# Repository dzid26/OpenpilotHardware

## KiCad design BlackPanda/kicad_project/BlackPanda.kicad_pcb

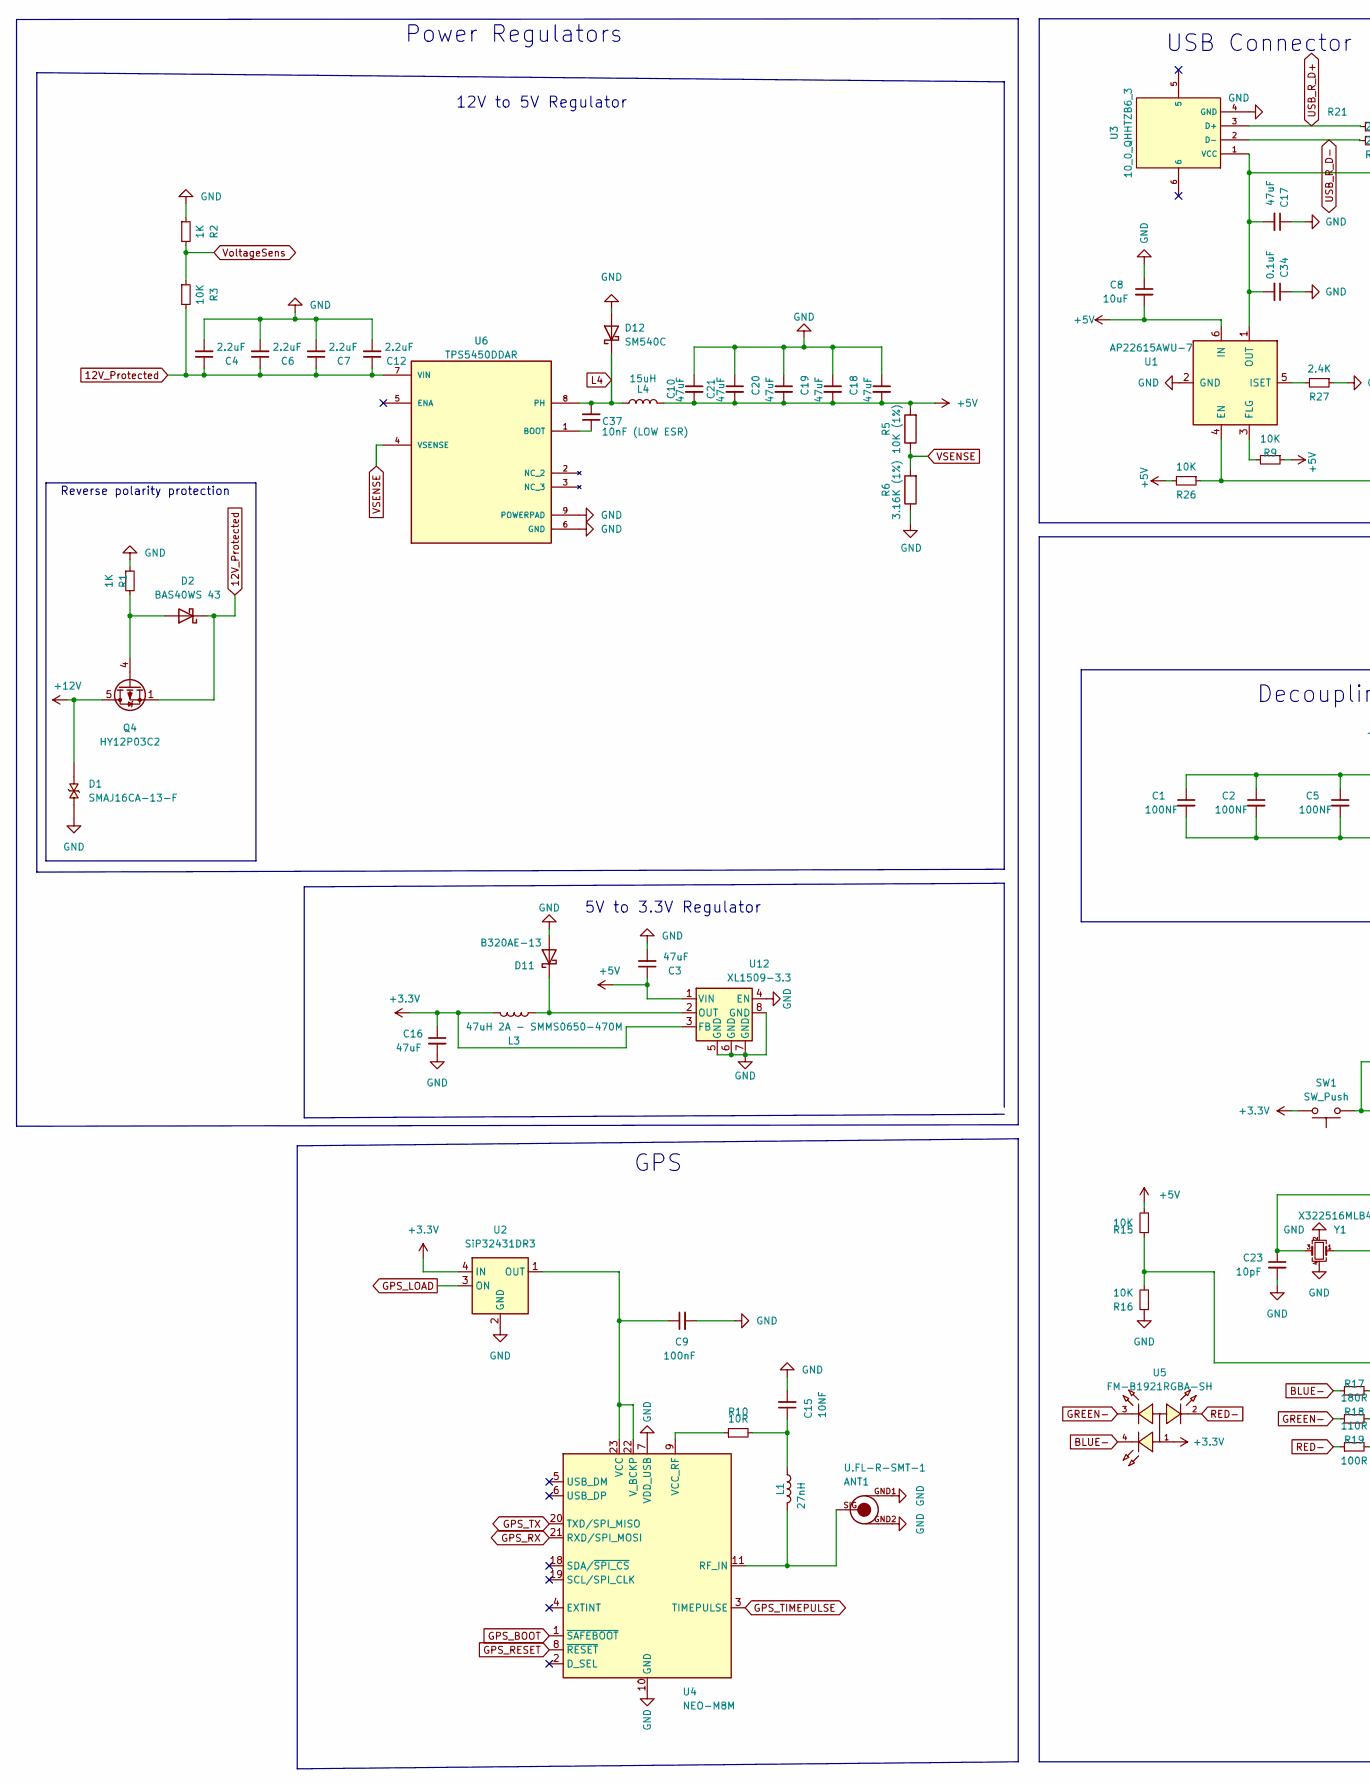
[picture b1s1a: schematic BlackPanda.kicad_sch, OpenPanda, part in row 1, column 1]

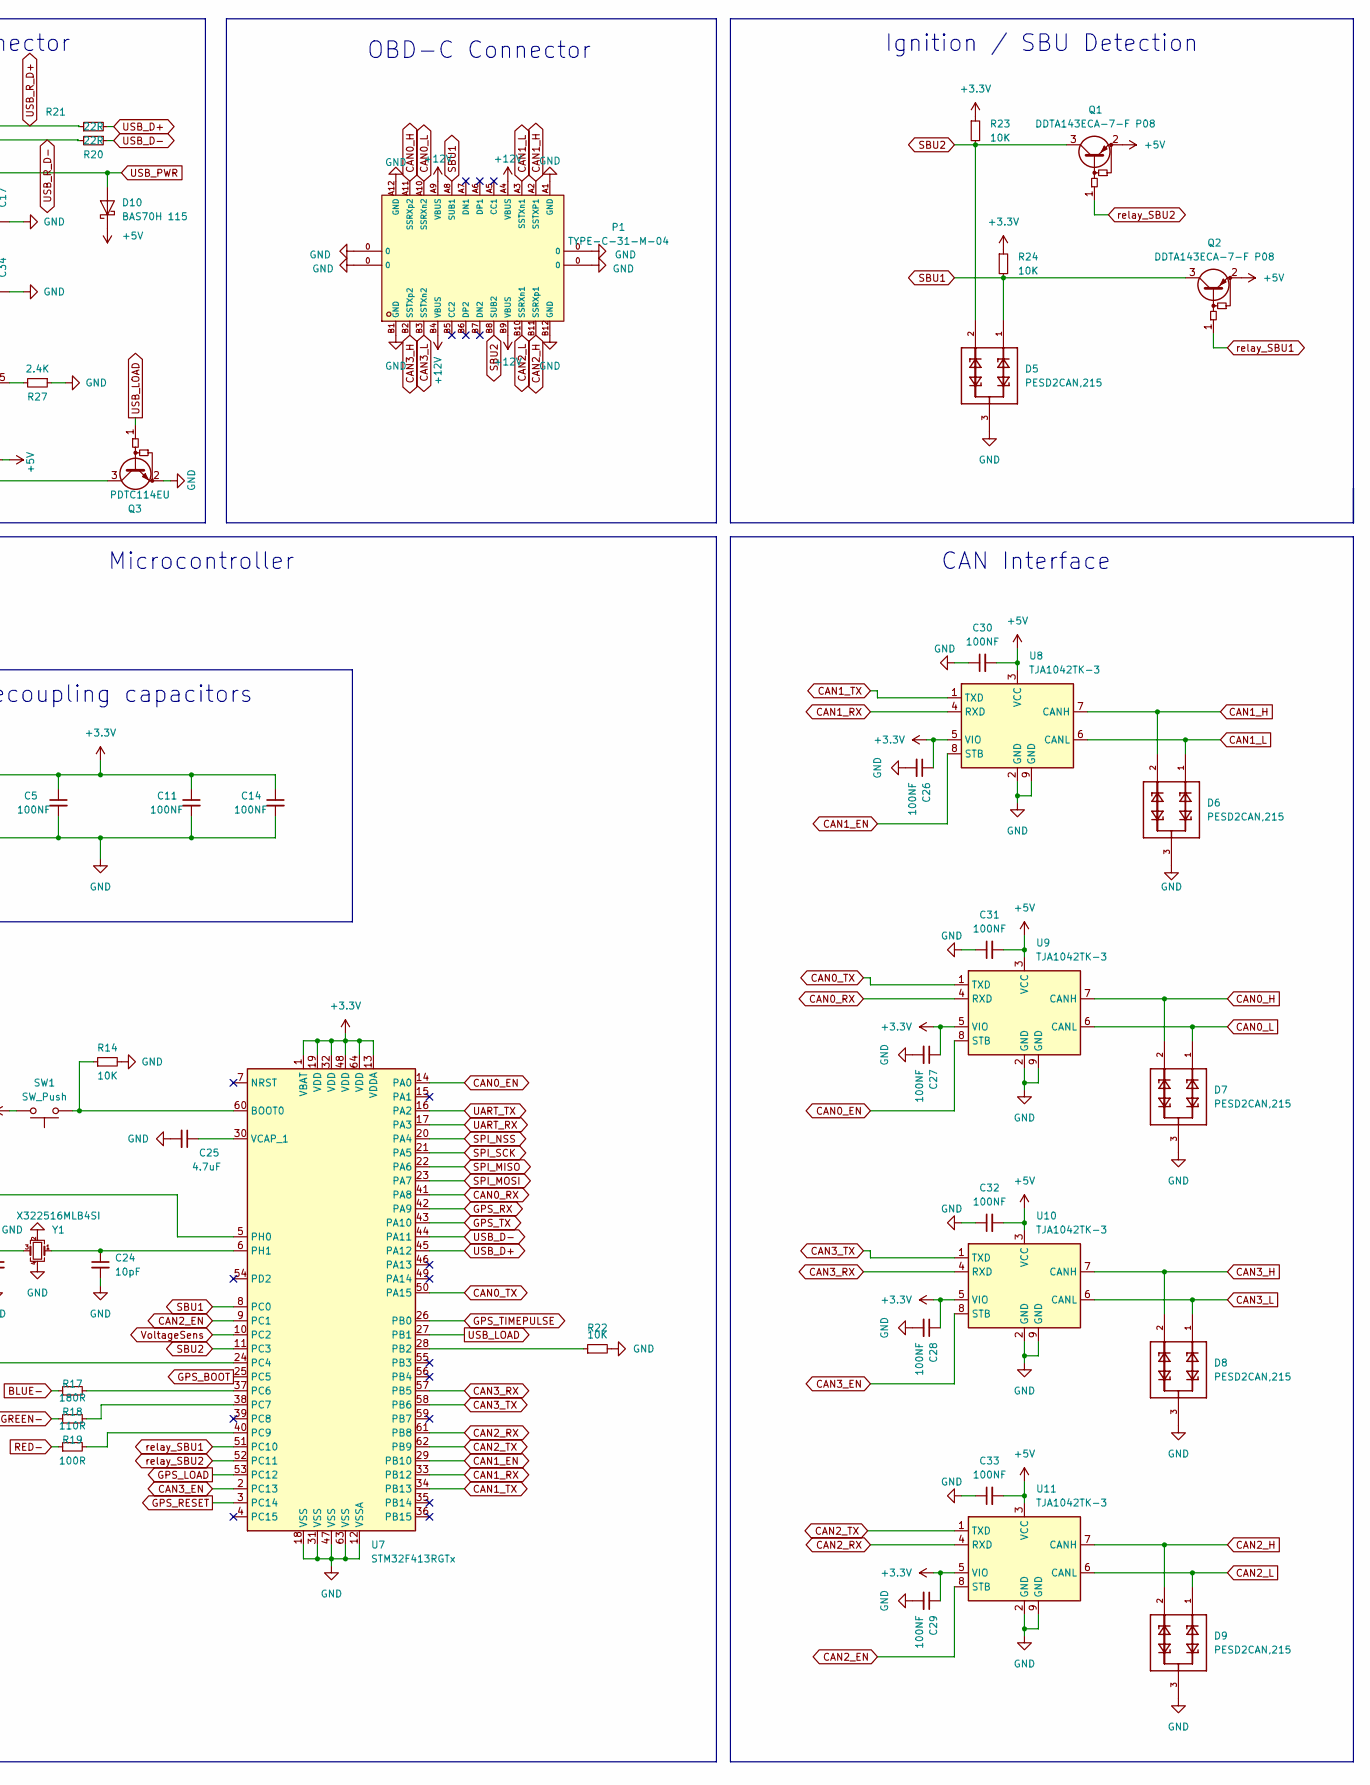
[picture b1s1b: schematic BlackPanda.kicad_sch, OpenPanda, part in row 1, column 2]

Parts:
ANT1: U.FL-R-SMT-1; PARTNUMBER U.FL-R-SMT(10)
C1, C2, C5, C11, C14, C26, C27, C28, C29, C30, C31, C32, C33: 100NF; C_0402_1005Metric
C3, C10, C16, C17, C18, C19, C20, C21: 47uF; C_0805_2012Metric
C4, C6, C7, C12: 2.2uF; C_0805_2012Metric
C8: 10uF; C_0402_1005Metric
C9: 100nF; C_0603_1608Metric
C15: 10NF; C_0402_1005Metric
C23, C24: 10pF; C_0402_1005Metric
C25: 4.7uF; C_0402_1005Metric
C34: 0.1uF; C_0402_1005Metric
C37: 10nF (LOW ESR); C_0402_1005Metric
D1: SMAJ16CA-13-F; DIOM4325X250N; PARTREV S2102
D2: BAS40WS 43; D_SOD-323
D5, D6, D7, D8, D9: PESD2CAN,215; SOT95P230X110-3N
D10: BAS70H 115; D_SOD-123F
D11: B320AE-13; D_SMA
D12: SM540C; D_SMC
L1: 27nH; L_0603_1608Metric
L3: 47uH 2A - SMMS0650-470M; IND-SMD_L7.3-W6.8; JLCPCB C149588
L4: 15uH; L_10.5x11.5_H4.0
P1: TYPE-C-31-M-04; USB-C-SMD_TYPE-C-USB-20; LCSC C129018
Q1, Q2: DDTA143ECA-7-F P08; SOT23-3
Q3: PDTC114EU; SOT-323_SC-70
Q4: HY12P03C2; PowerPAK_SO-8_Single
R1, R2: 1K; R_0402_1005Metric
R3, R9, R14, R15, R16, R22, R23, R24, R26: 10K; R_0402_1005Metric
R5: 10K (1%); R_0402_1005Metric
R6: 3.16K (1%); C_0603_1608Metric
R10: 10R; R_0402_1005Metric
R17: 180R; R_0402_1005Metric
R18: 110R; R_0402_1005Metric
R19: 100R; R_0402_1005Metric
R20, R21: 22R; R_0402_1005Metric
R27: 2.4K; R_0402_1005Metric
SW1: SW_Push; SW_SPST_SKQG_WithStem
U1: AP22615AWU-7; SOT-23-6
U2: SiP32431DR3; SOT-363_SC-70-6
U3: 10_0_QHHTZB6_3; USB-A-TH_10.0QHHTZB6.3; LCSC C668591
U4: NEO-M8M; ublox_NEO
U5: FM-B1921RGBA-SH; LED-ARRAY-SMD_4P-L2.2-W2.1-BR; LCSC C727904
U6: TPS5450DDAR; CONV_TPS5450DDAR; PARTREV D
U7: STM32F413RGTx; LQFP-64_10x10mm_P0.5mm
U8, U9, U10, U11: TJA1042TK-3; HVSON-8-1EP_3x3mm_P0.65mm_EP1.6x2.4mm
U12: XL1509-3.3; Diodes_PSOP-8
Y1: X322516MLB4SI; Crystal_SMD_3225-4Pin_3.2x2.5mm

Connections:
12V_Protected: C4.1, C6.1, C7.1, C12.1, D2.1 (K), Q4.1 (S), Q4.2 (S), Q4.3 (S), R3.2, U6.7 (VIN)
+3V3: C1.1, C2.1, C5.1, C11.1, C14.1, C16.1, C26.1, C27.1, C28.1, C29.1, L3.2, R23.1, R24.1, SW1.2, U2.4 (IN), U5.1 (+), U7.1 (VBAT), U7.13 (VDDA), U7.19 (VDD), U7.32 (VDD), U7.48 (VDD), U7.64 (VDD), U8.5 (VIO), U9.5 (VIO), U10.5 (VIO), U11.5 (VIO), U12.3 (FB)
+5V: C3.1, C8.2, C10.2, C18.2, C19.2, C20.2, C21.2, C30.2, C31.2, C32.2, C33.2, D10.1 (K), L4.2, Q1.2 (E), Q2.2 (E), R5.2, R9.1, R15.2, R26.2, U1.6 (IN), U8.3 (VCC), U9.3 (VCC), U10.3 (VCC), U11.3 (VCC), U12.1 (VIN)
+12V: D1.2, P1.A4 (VBUS), P1.A9 (VBUS), P1.B4 (VBUS), P1.B9 (VBUS), Q4.5 (D)
BLUE-: R17.1, U5.4 (B-)
CAN0_EN: U7.14 (PA0), U9.8 (STB)
CAN0_H: D7.2, P1.A11 (SSRXp2), U9.7 (CANH)
CAN0_L: D7.1, P1.A10 (SSRXn2), U9.6 (CANL)
CAN0_RX: U7.41 (PA8), U9.4 (RXD)
CAN0_TX: U7.50 (PA15), U9.1 (TXD)
CAN1_EN: U7.29 (PB10), U8.8 (STB)
CAN1_H: D6.2, P1.A2 (SSTXP1), U8.7 (CANH)
CAN1_L: D6.1, P1.A3 (SSTXn1), U8.6 (CANL)
CAN1_RX: U7.33 (PB12), U8.4 (RXD)
CAN1_TX: U7.34 (PB13), U8.1 (TXD)
CAN2_EN: U7.9 (PC1), U11.8 (STB)
CAN2_H: D9.2, P1.B11 (SSRXp1), U11.7 (CANH)
CAN2_L: D9.1, P1.B10 (SSRXn1), U11.6 (CANL)
CAN2_RX: U7.61 (PB8), U11.4 (RXD)
CAN2_TX: U7.62 (PB9), U11.1 (TXD)
CAN3_EN: U7.2 (PC13), U10.8 (STB)
CAN3_H: D8.2, P1.B2 (SSTXp2), U10.7 (CANH)
CAN3_L: D8.1, P1.B3 (SSTXn2), U10.6 (CANL)
CAN3_RX: U7.57 (PB5), U10.4 (RXD)
CAN3_TX: U7.58 (PB6), U10.1 (TXD)
GND: ANT1.GND1, ANT1.GND2, C1.2, C2.2, C3.2, C4.2, C5.2, C6.2, C7.2, C8.1, C9.2, C10.1, C11.2, C12.2, C14.2, C15.2, C16.2, C17.1, C18.1, C19.1, C20.1, C21.1, C23.2, C24.2, C25.2, C26.2, C27.2, C28.2, C29.2, C30.1, C31.1, C32.1, C33.1, C34.1, D1.1, D5.3, D6.3, D7.3, D8.3, D9.3, D11.2 (A), D12.2 (A), P1.0, P1.A1 (GND), P1.A12 (GND), P1.B1 (GND), P1.B12 (GND), Q3.2 (E), R1.1, R2.1, R6.1, R14.2, R16.1, R22.2, R27.1, U1.2 (GND), U2.2 (GND), U2.5 (GND), U3.4 (GND), U4.7 (VDD_USB), U4.10 (GND), U4.12 (GND), U4.13 (GND), U4.24 (GND), U6.6 (GND), U6.9 (POWERPAD), U7.12 (VSSA), U7.18 (VSS), U7.31 (VSS), U7.47 (VSS), U7.63 (VSS), U8.2 (GND), U8.9 (GND), U9.2 (GND), U9.9 (GND), U10.2 (GND), U10.9 (GND), U11.2 (GND), U11.9 (GND), U12.4 (EN), U12.5 (GND), U12.6 (GND), U12.7 (GND), U12.8 (GND), Y1.2, Y1.4
GPS_BOOT: U4.1 (~SAFEBOOT), U7.25 (PC5)
GPS_LOAD: U2.3 (ON), U7.53 (PC12)
GPS_RESET: U4.8 (~RESET), U7.3 (PC14)
GPS_RX: U4.21 (RXD/SPI_MOSI), U7.42 (PA9)
GPS_TIMEPULSE: U4.3 (TIMEPULSE), U7.26 (PB0)
GPS_TX: U4.20 (TXD/SPI_MISO), U7.43 (PA10)
GREEN-: R18.1, U5.3 (G-)
L4: C37.2, D12.1 (K), L4.1, U6.8 (PH)
unnamed: C15.1, L1.1, R10.2
unnamed: D2.2 (A), Q4.4 (G), R1.2
unnamed: D11.1 (K), L3.1, U12.2 (OUT)
unnamed: Q3.3 (C), R26.1, U1.4 (EN)
unnamed: R9.2, U1.3 (FLG)
unnamed: R27.2, U1.5 (ISET)
unnamed: C9.1, U2.1 (OUT), U4.22 (V_BCKP), U4.23 (VCC)
unnamed: ANT1.SIG, L1.2, U4.11 (RF_IN)
unnamed: R10.1, U4.9 (VCC_RF)
unnamed: C37.1, U6.1 (BOOT)
unnamed: R14.1, SW1.1, U7.60 (BOOT0)
unnamed: R22.1, U7.28 (PB2)
unnamed: R15.1, R16.2, U7.24 (PC4)
unnamed: R17.2, U7.37 (PC6)
unnamed: R18.2, U7.38 (PC7)
unnamed: R19.2, U7.40 (PC9)
unnamed: C23.1, U7.5 (PH0), Y1.3
unnamed: C24.1, U7.6 (PH1), Y1.1
unnamed: C25.1, U7.30 (VCAP_1)
RED-: R19.1, U5.2 (R-)
SBU1: D5.1, P1.A8 (SUB1), Q2.3 (C), R24.2, U7.8 (PC0)
SBU2: D5.2, P1.B8 (SUB2), Q1.3 (C), R23.2, U7.11 (PC3)
SPI_MISO: U7.22 (PA6)
SPI_MOSI: U7.23 (PA7)
SPI_NSS: U7.20 (PA4)
SPI_SCK: U7.21 (PA5)
UART_RX: U7.17 (PA3)
UART_TX: U7.16 (PA2)
USB_D+: R21.2, U7.45 (PA12)
USB_D-: R20.1, U7.44 (PA11)
USB_LOAD: Q3.1 (B), U7.27 (PB1)
USB_PWR: C17.2, C34.2, D10.2 (A), U1.1 (OUT), U3.1 (VCC)
USB_R_D+: R21.1, U3.3 (D+)
USB_R_D-: R20.2, U3.2 (D-)
VSENSE: R5.1, R6.2, U6.4 (VSENSE)
VoltageSens: R2.2, R3.1, U7.10 (PC2)
relay_SBU1: Q2.1 (B), U7.51 (PC10)
relay_SBU2: Q1.1 (B), U7.52 (PC11)

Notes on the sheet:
USB Connector
CAN Interface
5V to 3.3V Regulator
OBD-C Connector
Decoupling capacitors
Power Regulators
12V to 5V Regulator
Microcontroller
GPS
Ignition / SBU Detection
Reverse polarity protection

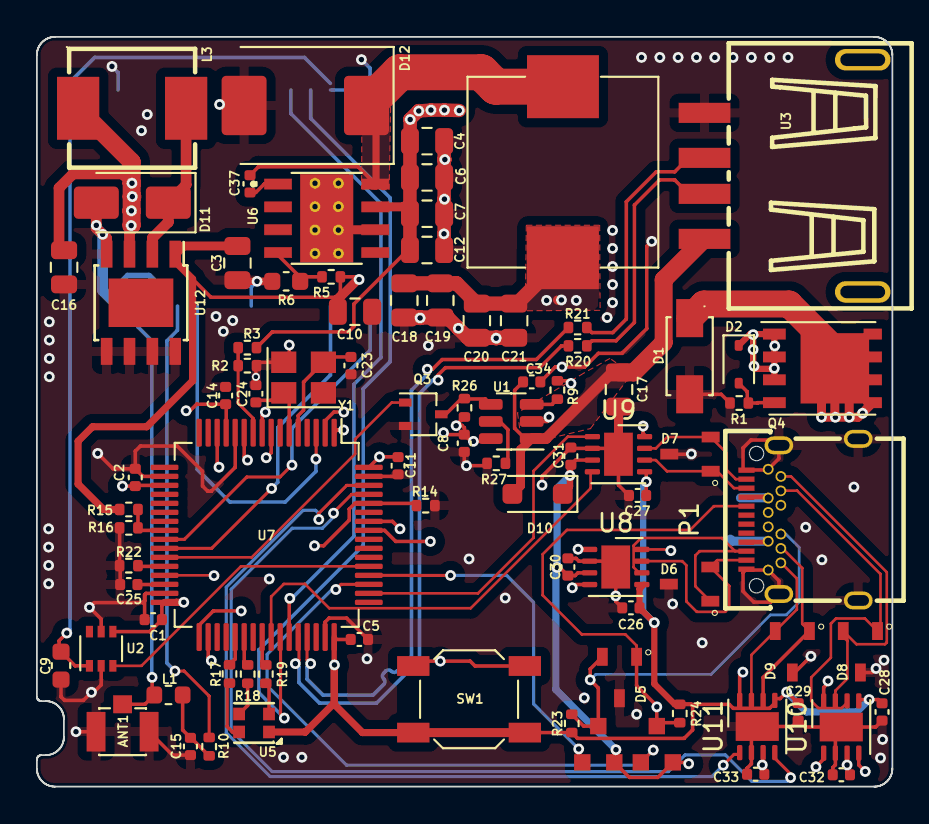
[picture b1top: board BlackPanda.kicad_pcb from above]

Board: 4 copper layers, 47.5 x 41.7 mm, 86 parts (1 on the bottom side), 66 nets.

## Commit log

2024-02-05 TJA1042 uses HVSON8
